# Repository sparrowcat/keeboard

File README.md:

# keeboard

Lol this will be my attempt at PCB design

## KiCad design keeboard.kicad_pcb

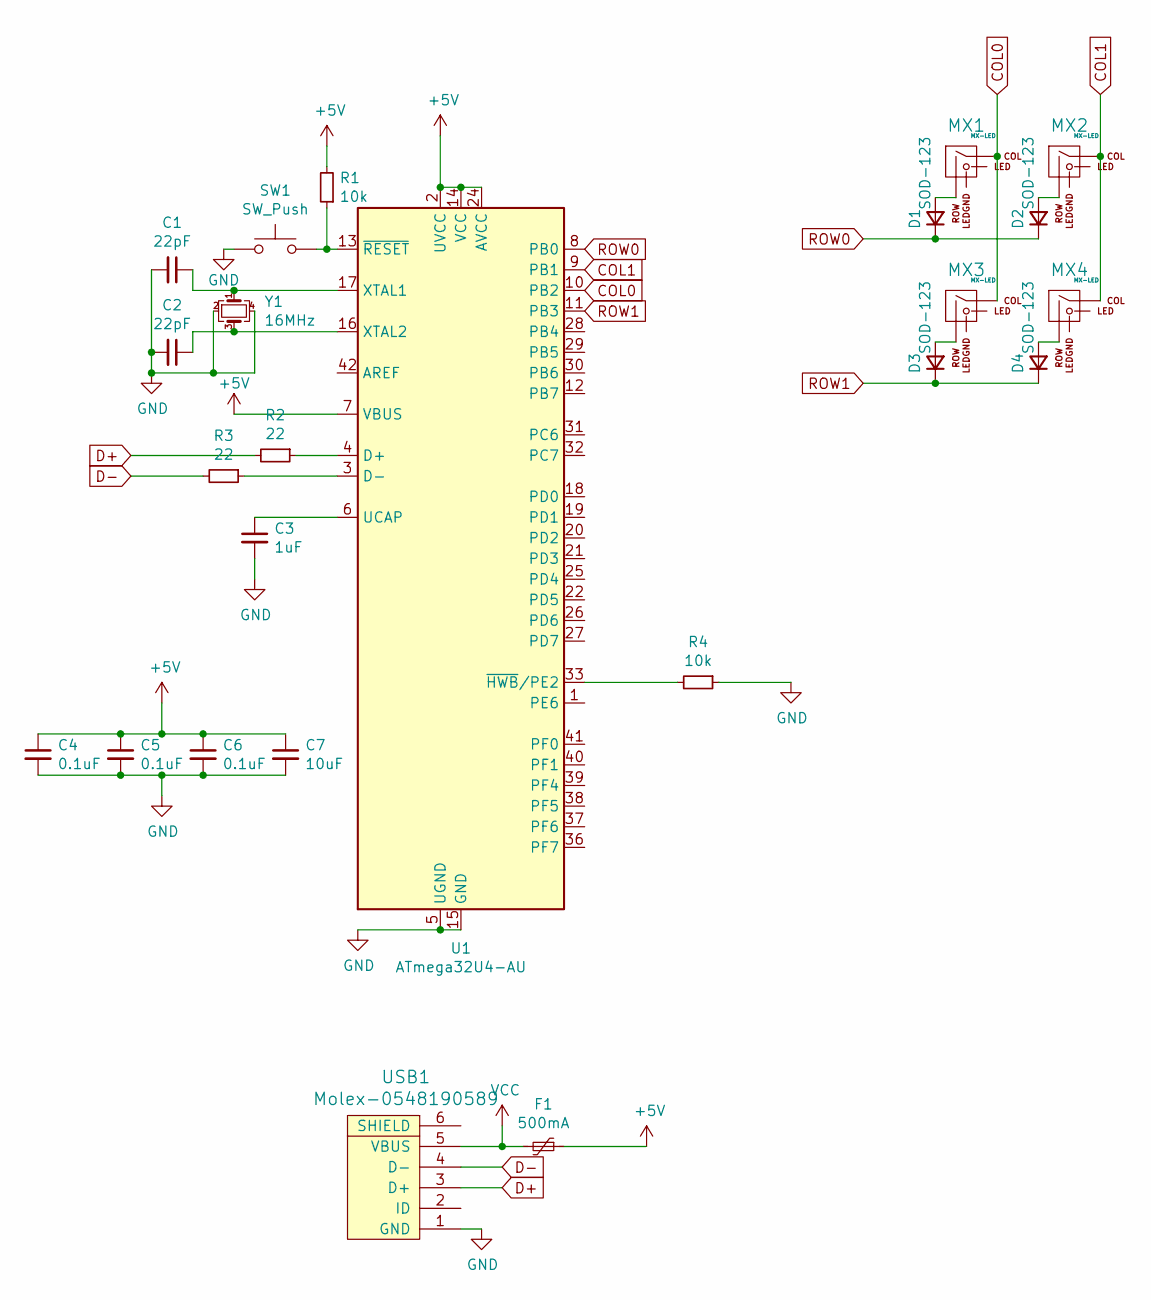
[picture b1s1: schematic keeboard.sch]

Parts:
C1, C2: 22pF; C_0805_2012Metric
C3: 1uF; C_0805_2012Metric
C4, C5, C6: 0.1uF; C_0805_2012Metric
C7: 10uF; C_0805_2012Metric
D1, D2, D3, D4: SOD-123; D_SOD-123
F1: 500mA; Fuse_1206_3216Metric
MX1, MX2, MX3, MX4: MX-LED; MX-1U
R1, R4: 10k; R_0805_2012Metric
R2, R3: 22; R_0805_2012Metric
SW1: SW_Push; SKQG-1155865
U1: ATmega32U4-AU; TQFP-44_10x10mm_P0.8mm
USB1: Molex-0548190589
Y1: 16MHz; Crystal_SMD_3225-4Pin_3.2x2.5mm

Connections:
+5V: C4.1, C5.1, C6.1, C7.1, F1.1, R1.2, U1.2 (UVCC), U1.7 (VBUS), U1.14 (VCC), U1.24 (AVCC), U1.34 (VCC), U1.44 (AVCC)
COL0: MX1.1 (COL), MX3.1 (COL), U1.10 (PB2)
COL1: MX2.1 (COL), MX4.1 (COL), U1.9 (PB1)
D+: R2.2, USB1.3 (D+)
D-: R3.2, USB1.4 (D-)
GND: C1.2, C2.2, C3.2, C4.2, C5.2, C6.2, C7.2, R4.1, SW1.1, U1.5 (UGND), U1.15 (GND), U1.23 (GND), U1.35 (GND), U1.43 (GND), USB1.1 (GND), Y1.2, Y1.4
unnamed: C1.1, U1.17 (XTAL1), Y1.1
unnamed: C2.1, U1.16 (XTAL2), Y1.3
unnamed: C3.1, U1.6 (UCAP)
unnamed: D1.2 (A), MX1.2 (ROW)
unnamed: D2.2 (A), MX2.2 (ROW)
unnamed: D3.2 (A), MX3.2 (ROW)
unnamed: D4.2 (A), MX4.2 (ROW)
unnamed: R1.1, SW1.2, U1.13 (~RESET)
unnamed: R2.1, U1.4 (D+)
unnamed: R3.1, U1.3 (D-)
unnamed: R4.2, U1.33 (~HWB~/PE2)
ROW0: D1.1 (K), D2.1 (K), U1.8 (PB0)
ROW1: D3.1 (K), D4.1 (K), U1.11 (PB3)
VCC: F1.2, USB1.5 (VBUS)

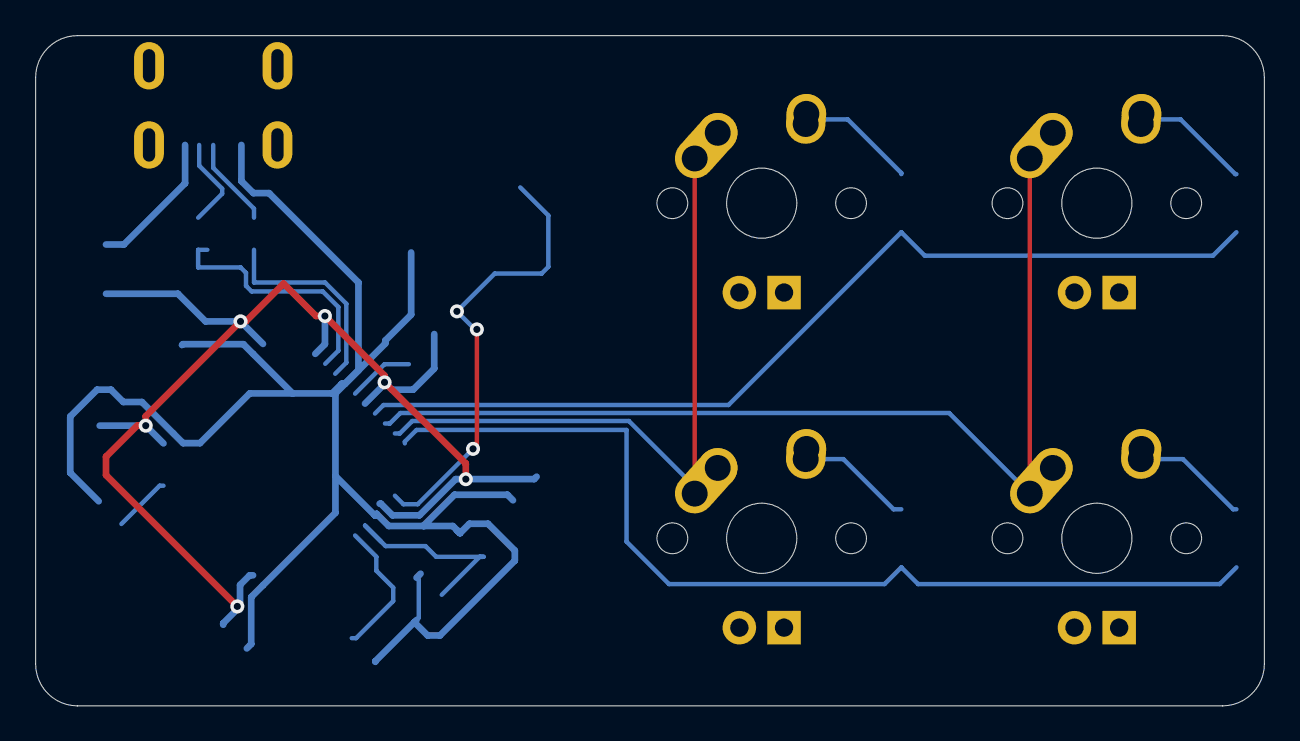
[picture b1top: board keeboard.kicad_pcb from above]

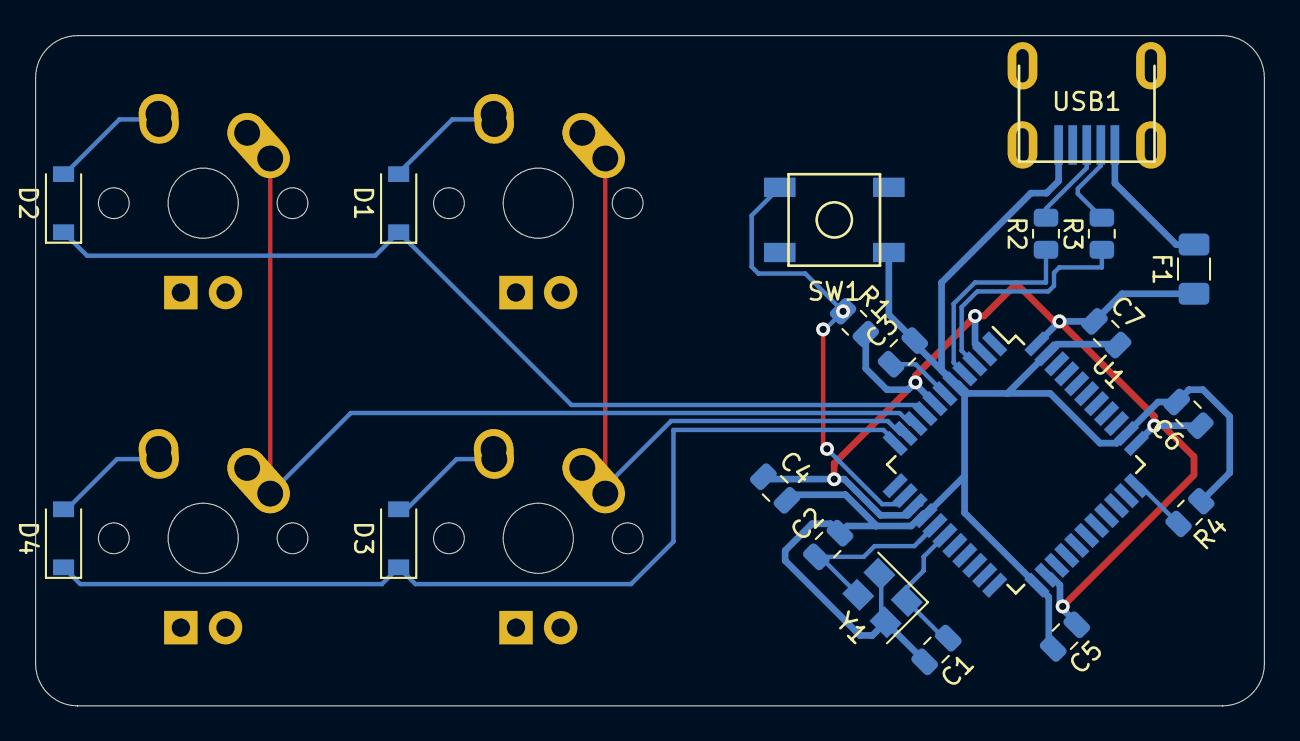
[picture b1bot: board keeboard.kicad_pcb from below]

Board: 2 copper layers, 69.8 x 38.1 mm, 24 parts (20 on the bottom side), 20 nets.

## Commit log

2021-02-02 initialize kicad project
2021-02-02 Add submodules
2021-02-02 add libraries to project
2021-02-02 made example schematic
2021-02-03 finished routing
2021-02-03 restructure to test board
2021-02-03 add eagle libraries?
2022-03-07 using kicad instad foss forever
